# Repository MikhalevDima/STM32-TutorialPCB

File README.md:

# [MSPM0-TutorialPCB]
Двухслойная печатная плата (PCB), спроектированная в **KiCad** с использованием методологии и лучших практик инженерного канала **Phil's Lab**.
## 📸 Визуализация устройства
## 🛠 Ключевые характеристики и компоненты
- **Микроконтроллер/Базовый чип:** STM32WB55CEU6.
- **Количество слоев:** 4 слоя.
- **Толщина платы / Финиш:** Разработано под стандартные 1.58 мм.
- **Интерфейсы и питание:** USB Type-C для питания и данных.
## 🚀 Что было реализовано в проекте (Инженерные навыки)
В процессе разработки этого устройства были применены следующие практики:
1. **Схемотехника и подбор компонентов:** Полный цикл отрисовки схемы, расчет номиналов обвязки (конденсаторы фильтрации, подтягивающие резисторы) на основе технической документации (Data Sheets).
2. **Интерактивная трассировка (KiCad):** Использование современных режимов трассировщика (*Shove*, *Walk Around*) для обеспечения плотного и аккуратного монтажа. С контролем импеданса 50 Ом.
3. **Цепи питания и заземления:** Организованы сплошные полигоны заземления (`GND`) для снижения помех, настроены корректные тепловые барьеры (*Thermal Reliefs*) для падов.
4. **Управление правилами проектирования (DRC):** Настроены классы цепей (*Net Classes*) и технологические зазоры (*Clearance*, *Margin*, *Courtyard*).
  ## 📁 Структура репозитория
- `/hardware` — исходные файлы проекта KiCad (`.kicad_sch`, `.kicad_pcb`).
- `/production` — итоговый пакет для завода:
  - `gerbers/` — файлы слоев в формате Gerber и файлы сверловки (`.drl`).
  - `bom/` — ведомость материалов (BOM) в формате CSV для закупки.
  - `position/` — файлы координат (`.pos`) для робота-установщика SMD.
- `/docs` — принципиальная схема в формате [PDF](docs/schematic.pdf) для быстрого просмотра (без необходимости открывать САПР).

---
*Проект разработан в учебных целях для демонстрации навыков проектирования современных печатных плат.*

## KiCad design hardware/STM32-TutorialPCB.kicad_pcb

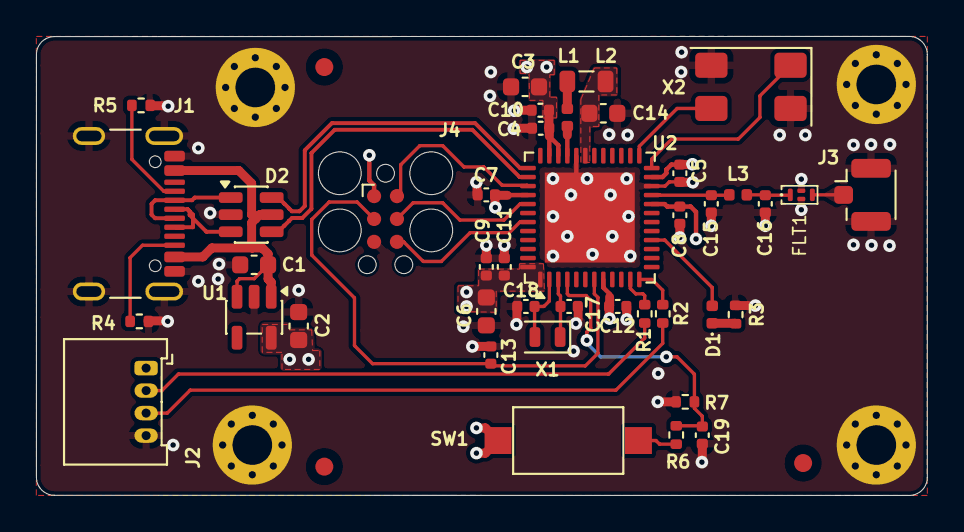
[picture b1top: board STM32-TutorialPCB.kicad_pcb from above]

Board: 4 copper layers, 49.5 x 25.5 mm, 48 parts (0 on the bottom side), 31 nets.

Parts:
C1, C2, C3, C6, C14: 4u7; C_0603_1608Metric
C4, C5, C7, C8, C9, C10, C11, C12, C13, C19: 100n; C_0402_1005Metric
C15: 0p8; C_0402_1005Metric
C16: 0p3; C_0402_1005Metric
C17, C18: 10p; C_0402_1005Metric
D1: LED; LED_0402_1005Metric
D2: USBLC6-2SC6; SOT-23-6
FLT1: DLF162500LT-5028A1
FM1, FM2, FM3: Fiducial; Fiducial_1mm_Mask2mm
H1, H2, H3, H4: MountingHole_Pad; MountingHole_2.2mm_M2_Pad_Via
J1: USB_C_Receptacle_USB2.0_16P; USB_C_Receptacle_GCT_USB4105-xx-A_16P_TopMnt_Horizontal
J2: Conn_01x04; Molex_PicoBlade_53048-0410_1x04_P1.25mm_Horizontal
J3: Conn_Coaxial; U.FL_Hirose_U.FL-R-SMT-1_Vertical
J4: TC2030; Tag-Connect_TC2030-IDC-FP_2x03_P1.27mm_Vertical
L1: 10n; L_0402_1005Metric
L2: 10u; L_0805_2012Metric
L3: 2n7; L_0402_1005Metric
R1, R2, R3, R6: 220R; R_0402_1005Metric
R4, R5, R7: 5k1; R_0402_1005Metric
SW1: SW_Push; SW_SPST_CK_RS282G05A3
U1: MIC5365-3.3YD5; TSOT-23-5
U2: STM32WB55CEU6; QFN-48-1EP_7x7mm_P0.5mm_EP5.6x5.6mm
X1: 32kHz768; Crystal_SMD_2012-2Pin_2.0x1.2mm
X2: 32MHz; Crystal_SMD_0603-4Pin_6.0x3.5mm

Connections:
+3V3: C2.1, C3.1, C4.1, C5.1, C6.1, C7.1, C8.1, C9.1, C10.1, C11.1, C12.1, J2.1, J4.1 (VCC), SW1.2, U1.5 (VOUT), U2.1 (VBAT), U2.8 (VDDA), U2.20 (VDD), U2.23 (VDDRF), U2.34 (VDDSMPS), U2.35 (VDD), U2.40 (VDDUSB), U2.48 (VDD)
/+VBUS: C1.1, D2.5 (VBUS), J1.A4 (VBUS), J1.A9 (VBUS), U1.1 (VIN), U1.3 (EN)
/BOOT0: C19.1, R6.1, R7.1, U2.4 (PH3)
/HSE_IN: U2.25 (OSC_IN), X2.3
/HSE_OUT: U2.24 (OSC_OUT), X2.1
/LSE_IN: C18.1, U2.2 (PC14), X1.2
/LSE_OUT: C17.1, U2.3 (PC15), X1.1
/RF: C15.1, L3.1, U2.21 (RF1)
/RF_ANT: FLT1.3 (OUT), J3.1 (In)
/RF_MATCH: C16.1, FLT1.1 (IN), L3.2
/SMPSFB: C14.1, L2.2, U2.31 (VFBSMPS)
/SMPSLX: L1.1, U2.33 (VLXSMPS)
/SMPSLXL: L1.2, L2.1
/SWCLK: J4.4 (SWCLK), U2.41 (PA14)
/SWDDIO: J4.2 (SWDIO), U2.39 (PA13)
/SWD_NRST: C13.1, J4.3 (~RESET), U2.7 (NRST)
/SWO: J4.6 (SWO), U2.43 (PB3)
/UART_RX: R2.2, U2.12 (PA3)
/UART_RXC: J2.3, R2.1
/UART_TX: R1.2, U2.11 (PA2)
/UART_TXC: J2.2, R1.1
/USB_D+: D2.4 (I/O2), U2.38 (PA12)
/USB_D-: D2.6 (I/O1), U2.37 (PA11)
GND: C1.2, C2.2, C3.2, C4.2, C5.2, C6.2, C7.2, C8.2, C9.2, C10.2, C11.2, C12.2, C13.2, C14.2, C15.2, C16.2, C17.2, C18.2, C19.2, D2.2 (GND), FLT1.2 (GND), FLT1.4 (GND), H1.1 (1_1), H2.1 (1_1), H3.1 (1_1), H4.1 (1_1), J1.A1 (GND), J1.A12 (GND), J1.SH (SHIELD), J2.4, J3.2 (Ext), J4.5 (GND), R3.1, R4.2, R5.2, R7.2, U1.2 (GND), U2.22 (VSSRF), U2.32 (VSSSMPS), U2.49 (VSS), X2.2 (G), X2.4 (G)
unnamed: D1.2 (A), U2.16 (PA7)
unnamed: D1.1 (K), R3.2
unnamed: D2.1 (I/O1), J1.A7 (D-), J1.B7 (D-)
unnamed: D2.3 (I/O2), J1.A6 (D+), J1.B6 (D+)
unnamed: J1.A5 (CC1), R5.1
unnamed: J1.B5 (CC2), R4.1
unnamed: R6.2, SW1.1
